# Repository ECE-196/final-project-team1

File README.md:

# Final Project

This is where you and your team will place design documents, notes, research, etc.

We want to see your individual contributions and progress over time, so make sure each of
you contribute substantially. We will look at the commit history to see your contributions.

# Submission

1. All your work!

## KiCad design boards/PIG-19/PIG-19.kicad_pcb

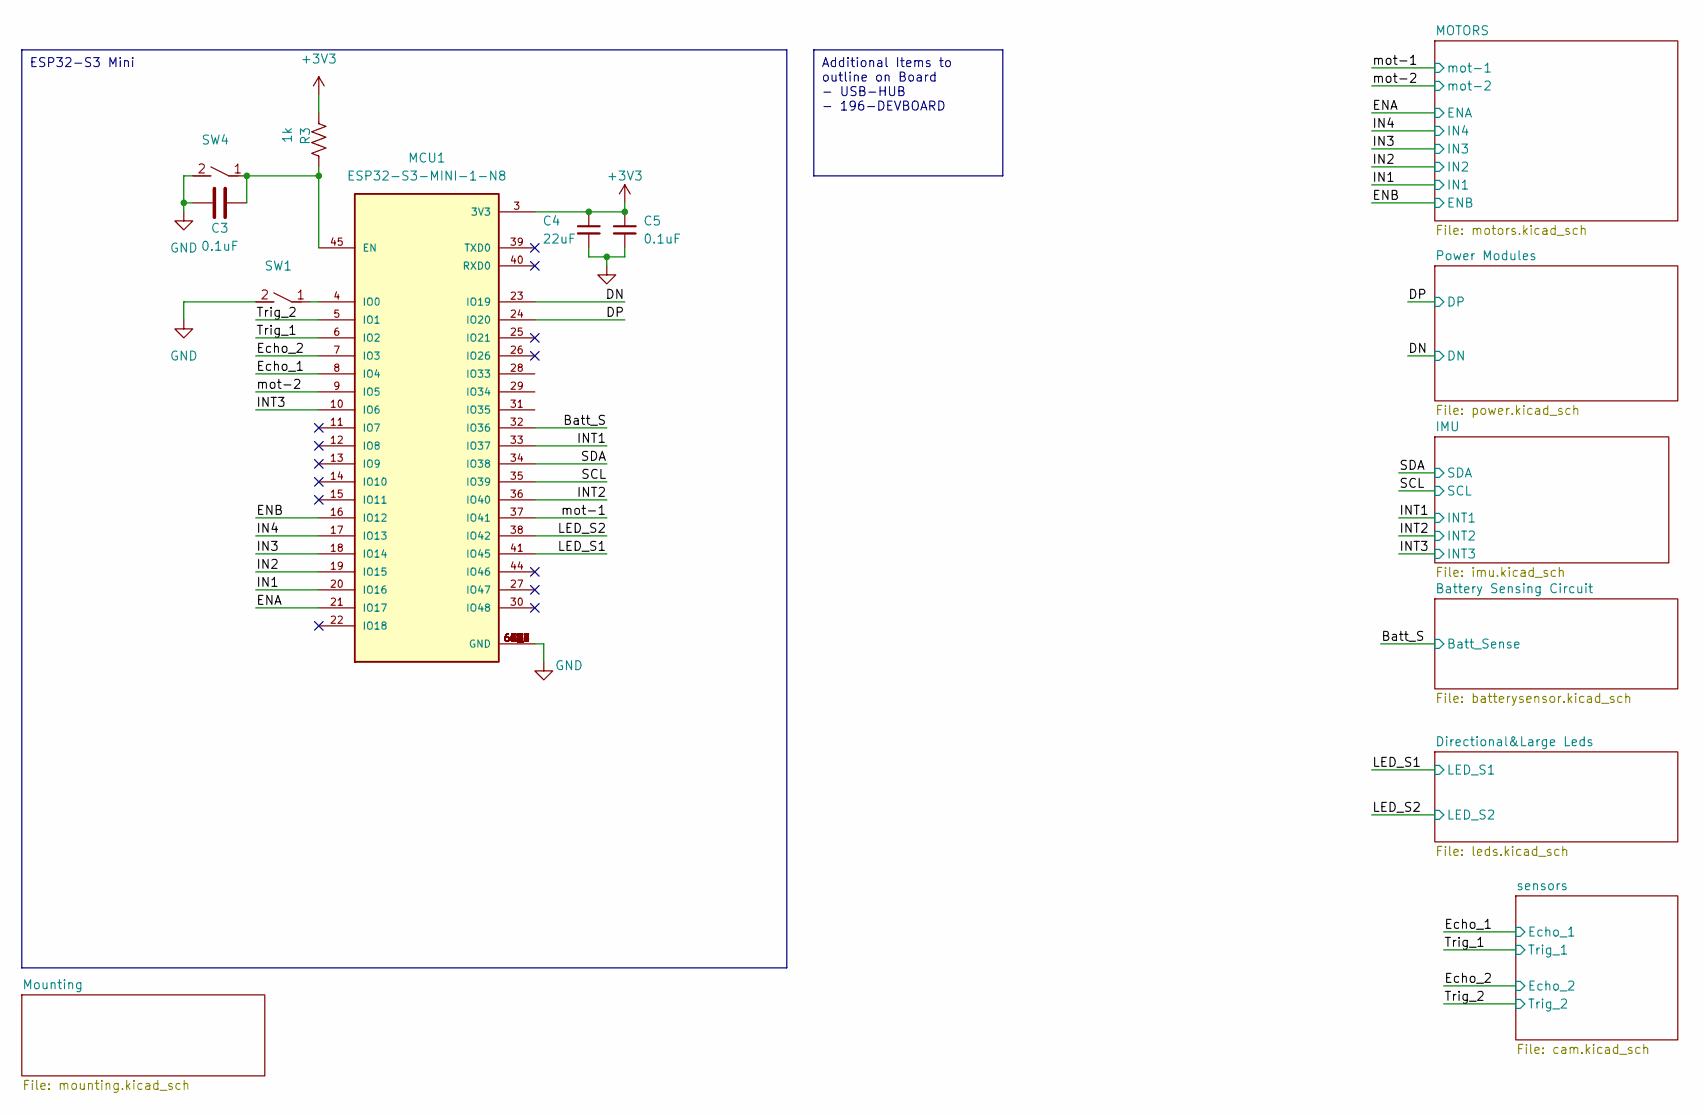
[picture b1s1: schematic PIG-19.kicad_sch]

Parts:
C3, C5: 0.1uF; C_0603_1608Metric
C4: 22uF; C_0603_1608Metric
MCU1: ESP32-S3-MINI-1-N8; XCVR_ESP32-S3-MINI-1-N8; PARTREV v0.6
R3: 1k; R_0603_1608Metric
SW1, SW4: rockerSwitch-434133025816

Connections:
+3V3: C4.1, C5.1, MCU1.3 (3V3), R3.2; also elsewhere on the board
/Batt_S: MCU1.32 (IO36); also elsewhere on the board
/DN: MCU1.23 (IO19); also elsewhere on the board
/DP: MCU1.24 (IO20); also elsewhere on the board
/ENA: MCU1.21 (IO17); also elsewhere on the board
/ENB: MCU1.16 (IO12); also elsewhere on the board
/Echo_1: MCU1.8 (IO4); also elsewhere on the board
/Echo_2: MCU1.7 (IO3); also elsewhere on the board
/IN1: MCU1.20 (IO16); also elsewhere on the board
/IN2: MCU1.19 (IO15); also elsewhere on the board
/IN3: MCU1.18 (IO14); also elsewhere on the board
/IN4: MCU1.17 (IO13); also elsewhere on the board
/INT1: MCU1.33 (IO37); also elsewhere on the board
/INT2: MCU1.36 (IO40); also elsewhere on the board
/INT3: MCU1.10 (IO6); also elsewhere on the board
/LED_S1: MCU1.41 (IO45); also elsewhere on the board
/LED_S2: MCU1.38 (IO42); also elsewhere on the board
/SCL: MCU1.35 (IO39); also elsewhere on the board
/SDA: MCU1.34 (IO38); also elsewhere on the board
/Trig_1: MCU1.6 (IO2); also elsewhere on the board
/Trig_2: MCU1.5 (IO1); also elsewhere on the board
/mot-1: MCU1.37 (IO41); also elsewhere on the board
/mot-2: MCU1.9 (IO5); also elsewhere on the board
GND: C3.1, C4.2, C5.2, MCU1.1 (GND), MCU1.2 (GND), MCU1.42 (GND), MCU1.43 (GND), MCU1.46 (GND), MCU1.47 (GND), MCU1.48 (GND), MCU1.49 (GND), MCU1.50 (GND), MCU1.51 (GND), MCU1.52 (GND), MCU1.53 (GND), MCU1.54 (GND), MCU1.55 (GND), MCU1.56 (GND), MCU1.57 (GND), MCU1.58 (GND), MCU1.59 (GND), MCU1.60 (GND), MCU1.61 (GND), MCU1.61_1 (GND), MCU1.61_2 (GND), MCU1.61_3 (GND), MCU1.61_4 (GND), MCU1.61_5 (GND), MCU1.61_6 (GND), MCU1.61_7 (GND), MCU1.61_8 (GND), MCU1.62 (GND), MCU1.63 (GND), MCU1.64 (GND), MCU1.65 (GND), SW1.2, SW4.2; also elsewhere on the board
unnamed: C3.2, MCU1.45 (EN), R3.1, SW4.1
unnamed: MCU1.4 (IO0), SW1.1

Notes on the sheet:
ESP32-S3 Mini
Additional Items to outline on Board - USB-HUB - 196-DEVBOARD

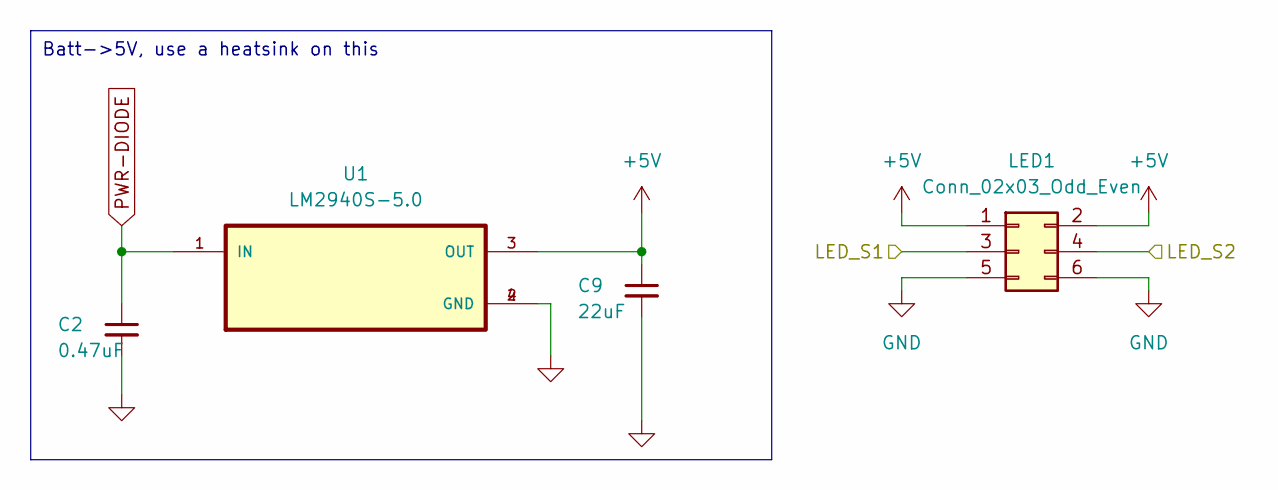
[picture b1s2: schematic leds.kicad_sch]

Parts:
C2: 0.47uF; C_0603_1608Metric
C9: 22uF; C_0603_1608Metric
LED1: Conn_02x03_Odd_Even; PinHeader_2x03_P2.54mm_Horizontal
U1: LM2940S-5.0; TO254P1524X483-4N

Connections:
+5V: C9.1, LED1.1, LED1.2, U1.3 (OUT); also elsewhere on the board
/LED_S1: LED1.3; also elsewhere on the board
/LED_S2: LED1.4; also elsewhere on the board
GND: C2.2, C9.2, LED1.5, LED1.6, U1.2 (GND), U1.4 (GND); also elsewhere on the board
PWR-DIODE: C2.1, U1.1 (IN); also elsewhere on the board

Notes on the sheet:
Batt->5V, use a heatsink on this

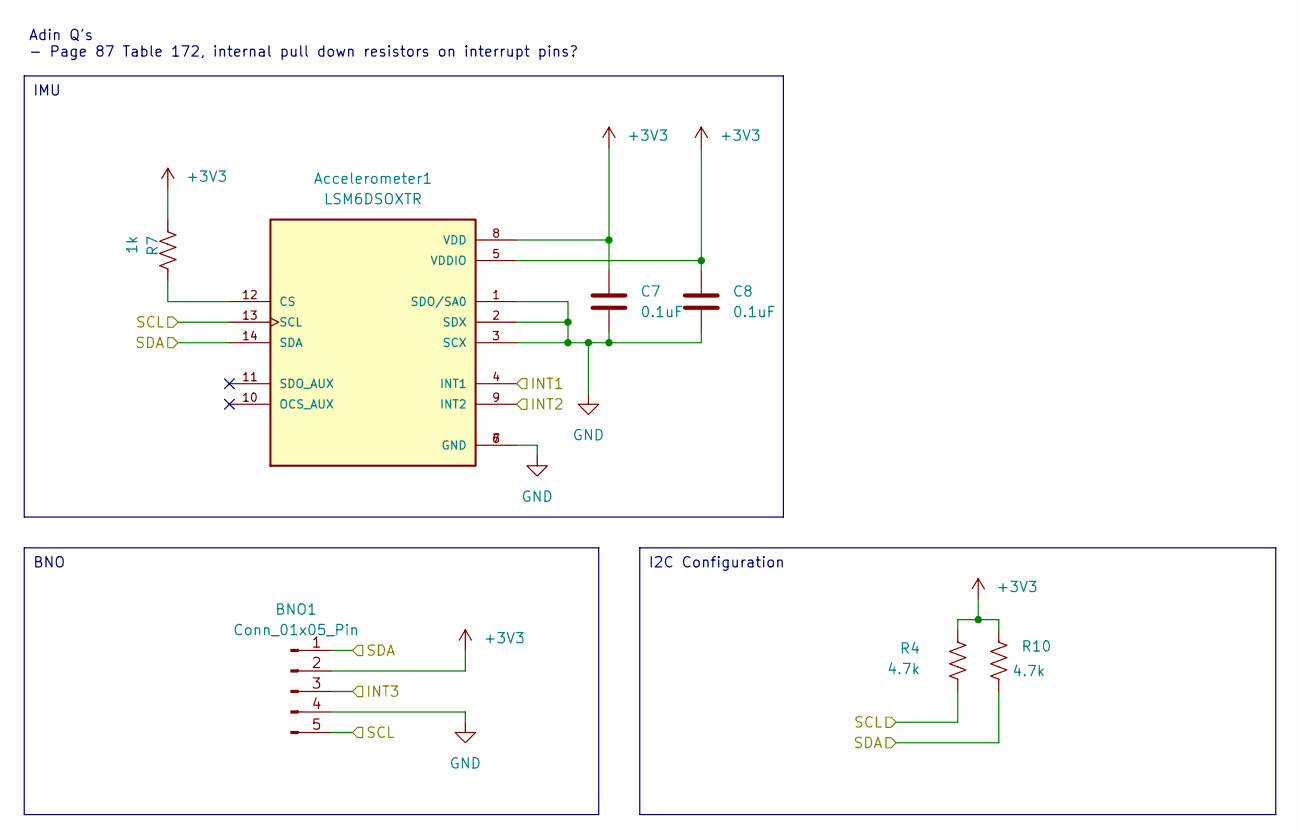
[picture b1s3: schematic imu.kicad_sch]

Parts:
Accelerometer1: LSM6DSOXTR; PQFN50P250X300X86-14N; PARTREV 3.0
BNO1: Conn_01x05_Pin; PinHeader_1x05_P2.54mm_Vertical
C7, C8: 0.1uF; C_0603_1608Metric
R4, R10: 4.7k; R_0603_1608Metric
R7: 1k; R_0603_1608Metric

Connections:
+3V3: Accelerometer1.5 (VDDIO), Accelerometer1.8 (VDD), BNO1.2, C7.1, C8.1, R4.2, R7.2, R10.2; also elsewhere on the board
/INT1: Accelerometer1.4 (INT1); also elsewhere on the board
/INT2: Accelerometer1.9 (INT2); also elsewhere on the board
/INT3: BNO1.3; also elsewhere on the board
/SCL: Accelerometer1.13 (SCL), BNO1.5, R4.1; also elsewhere on the board
/SDA: Accelerometer1.14 (SDA), BNO1.1, R10.1; also elsewhere on the board
GND: Accelerometer1.1 (SDO/SA0), Accelerometer1.2 (SDX), Accelerometer1.3 (SCX), Accelerometer1.6 (GND), Accelerometer1.7 (GND), BNO1.4, C7.2, C8.2; also elsewhere on the board
unnamed: Accelerometer1.12 (CS), R7.1

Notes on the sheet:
I2C Configuration
BNO
IMU
Adin Q's - Page 87 Table 172, internal pull down resistors on interrupt pins?

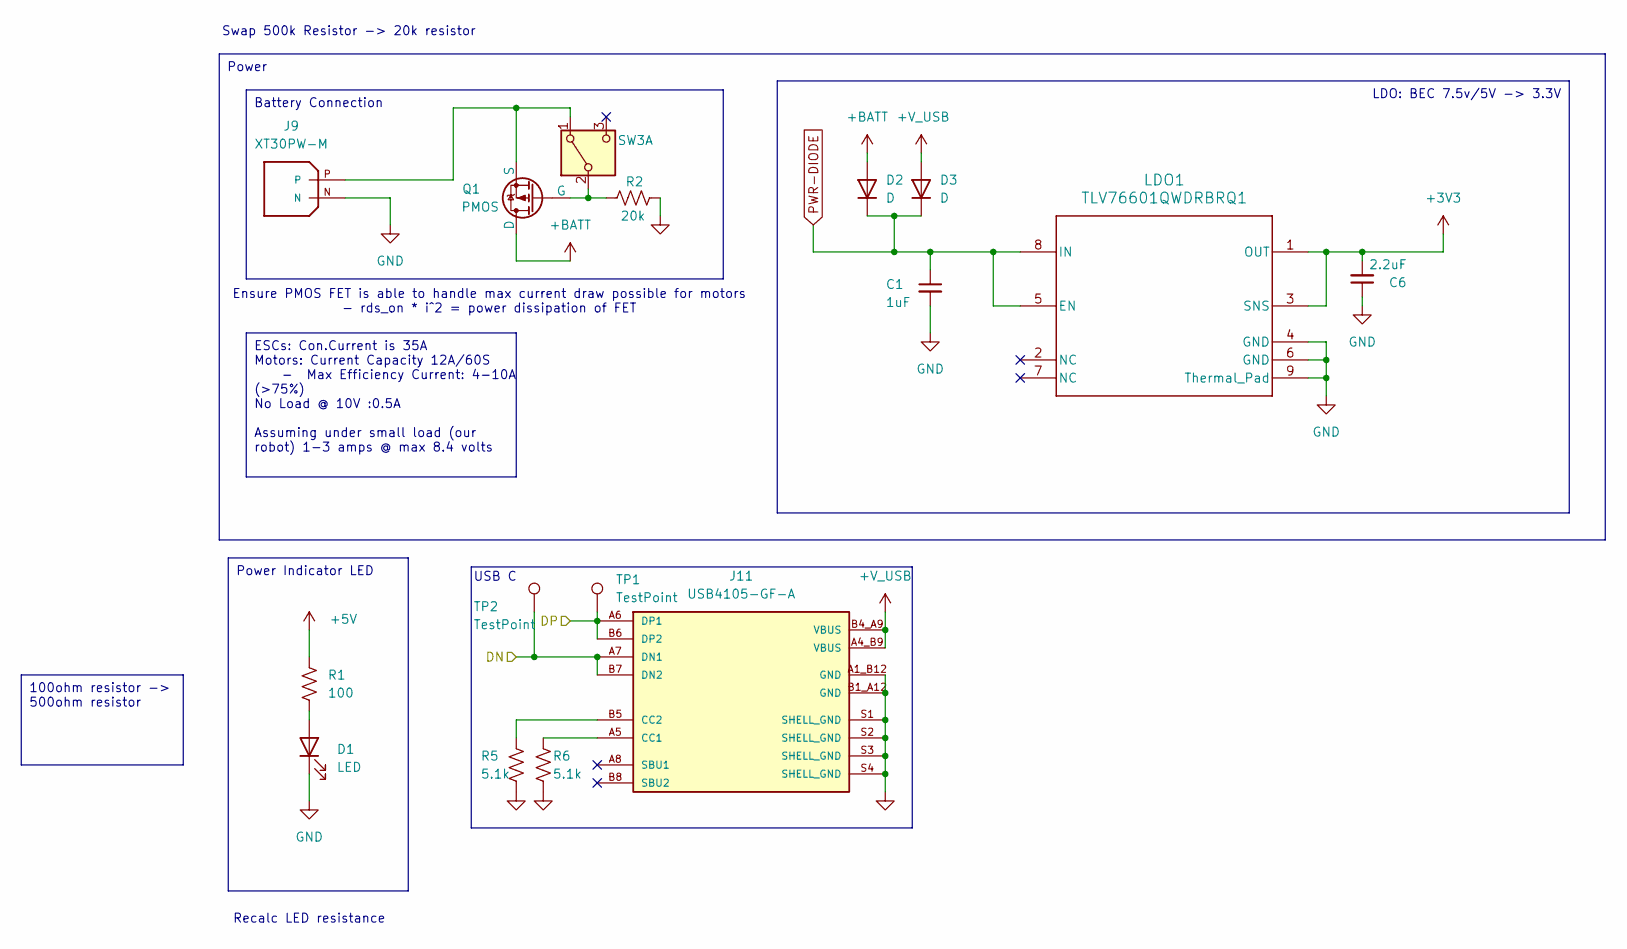
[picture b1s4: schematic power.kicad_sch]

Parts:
C1: 1uF; C_0603_1608Metric
C6: 2.2uF; C_0603_1608Metric
D1: LED; LED_0603_1608Metric
D2, D3: D; D_SOD-123F
J9: XT30PW-M; AMASS_XT30PW-M; PARTREV 1.2
J11: USB4105-GF-A; GCT_USB4105-GF-A; PARTREV A3
LDO1: TLV76601QWDRBRQ1; DRB0008J-IPC_A
Q1: PMOS; PowerPAK_SO-8_Single
R1: 100; R_0603_1608Metric
R2: 20k; R_0603_1608Metric
R5, R6: 5.1k; R_0603_1608Metric
SW3: SW_Nidec_CAS-120A1; SW_JS102011JAQN
TP1, TP2: TestPoint; TestPoint_Pad_D2.0mm

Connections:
+3V3: C6.2, LDO1.1 (OUT), LDO1.3 (SNS); also elsewhere on the board
+5V: R1.1; also elsewhere on the board
+BATT: D2.2 (A), Q1.5 (D); also elsewhere on the board
+V_USB: D3.2 (A), J11.A4_B9 (VBUS), J11.B4_A9 (VBUS)
/DN: J11.A7 (DN1), J11.B7 (DN2), TP2.1; also elsewhere on the board
/DP: J11.A6 (DP1), J11.B6 (DP2), TP1.1; also elsewhere on the board
GND: C1.2, C6.1, D1.1 (K), J9.N, J11.A1_B12 (GND), J11.B1_A12 (GND), J11.S1 (SHELL_GND), J11.S2 (SHELL_GND), J11.S3 (SHELL_GND), J11.S4 (SHELL_GND), LDO1.4 (GND), LDO1.6 (GND), LDO1.9 (Thermal_Pad), R2.2, R5.2, R6.2; also elsewhere on the board
unnamed: D1.2 (A), R1.2
unnamed: J11.A5 (CC1), R6.1
unnamed: J11.B5 (CC2), R5.1
unnamed: Q1.4 (G), R2.1, SW3.2 (B)
unnamed: J9.P, Q1.1 (S), Q1.2 (S), Q1.3 (S), SW3.1 (A)
PWR-DIODE: C1.1, D2.1 (K), D3.1 (K), LDO1.5 (EN), LDO1.8 (IN); also elsewhere on the board

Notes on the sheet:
LDO: BEC 7.5v/5V -> 3.3V
Battery Connection
100ohm resistor -> 500ohm resistor
ESCs: Con.Current is 35A Motors: Current Capacity 12A/60S - Max Efficiency Current: 4-10A (>75%) No Load @ 10V :0.5A Assuming under small load (our robot) 1-3 amps @ max 8.4 volts
Power Indicator LED
Power
Swap 500k Resistor -> 20k resistor
Recalc LED resistance
Ensure PMOS FET is able to handle max current draw possible for motors - rds_on * i^2 = power dissipation of FET
USB C

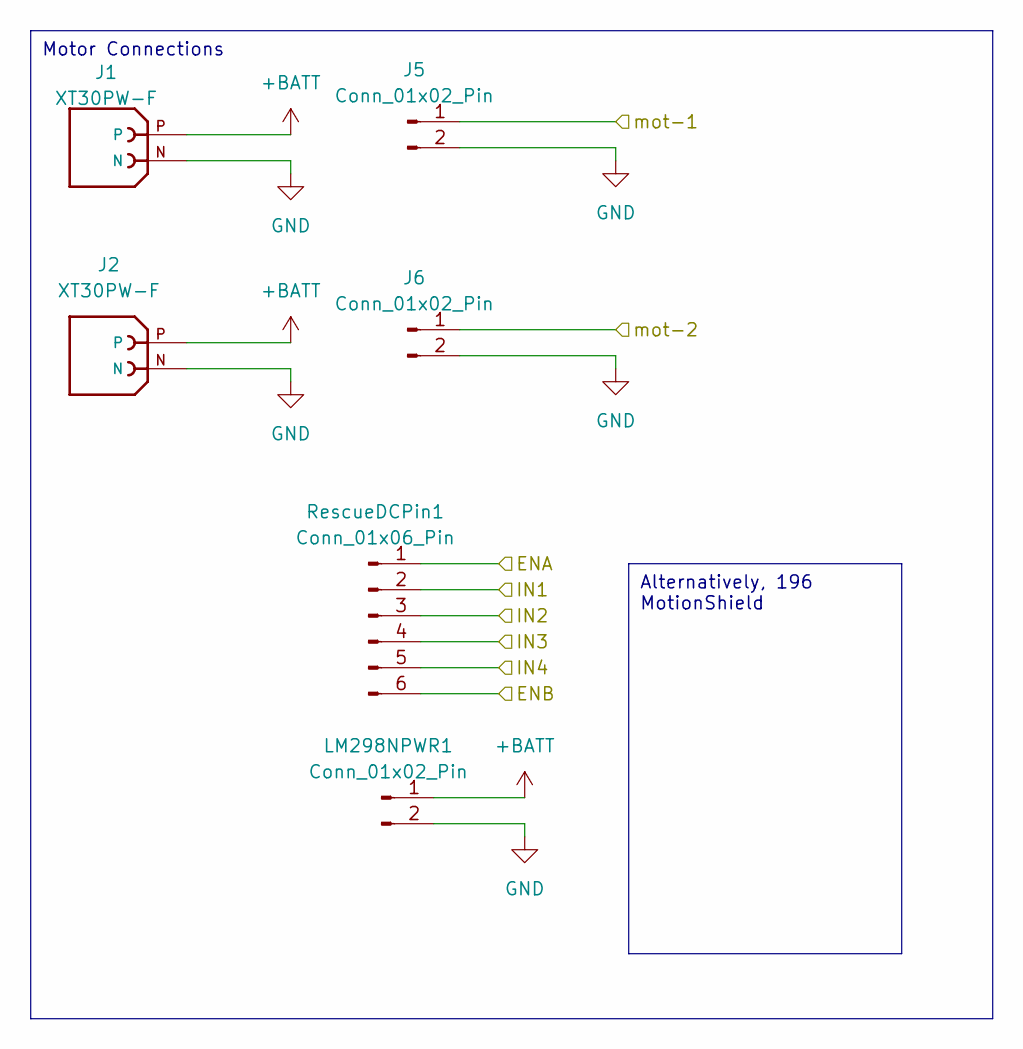
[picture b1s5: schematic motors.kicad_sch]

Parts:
J1, J2: XT30PW-F; AMASS_XT30PW-F; PARTREV 1.2
J5, J6: Conn_01x02_Pin; PinHeader_1x02_P2.54mm_Horizontal
LM298NPWR1: Conn_01x02_Pin; PinHeader_1x02_P2.54mm_Vertical
RescueDCPin1: Conn_01x06_Pin; PinHeader_1x06_P2.54mm_Vertical

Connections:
+BATT: J1.P, J2.P, LM298NPWR1.1; also elsewhere on the board
/ENA: RescueDCPin1.1; also elsewhere on the board
/ENB: RescueDCPin1.6; also elsewhere on the board
/IN1: RescueDCPin1.2; also elsewhere on the board
/IN2: RescueDCPin1.3; also elsewhere on the board
/IN3: RescueDCPin1.4; also elsewhere on the board
/IN4: RescueDCPin1.5; also elsewhere on the board
/mot-1: J5.1; also elsewhere on the board
/mot-2: J6.1; also elsewhere on the board
GND: J1.N, J2.N, J5.2, J6.2, LM298NPWR1.2; also elsewhere on the board

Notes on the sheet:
Motor Connections
Alternatively, 196 MotionShield

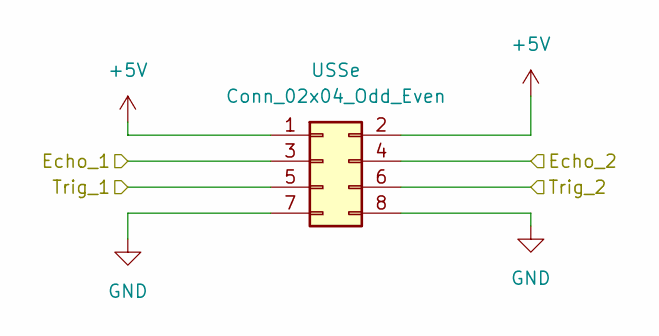
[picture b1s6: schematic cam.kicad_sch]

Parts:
USSe: Conn_02x04_Odd_Even; PinHeader_2x04_P2.54mm_Horizontal

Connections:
unnamed: USSe.1, USSe.2
unnamed: USSe.7, USSe.8

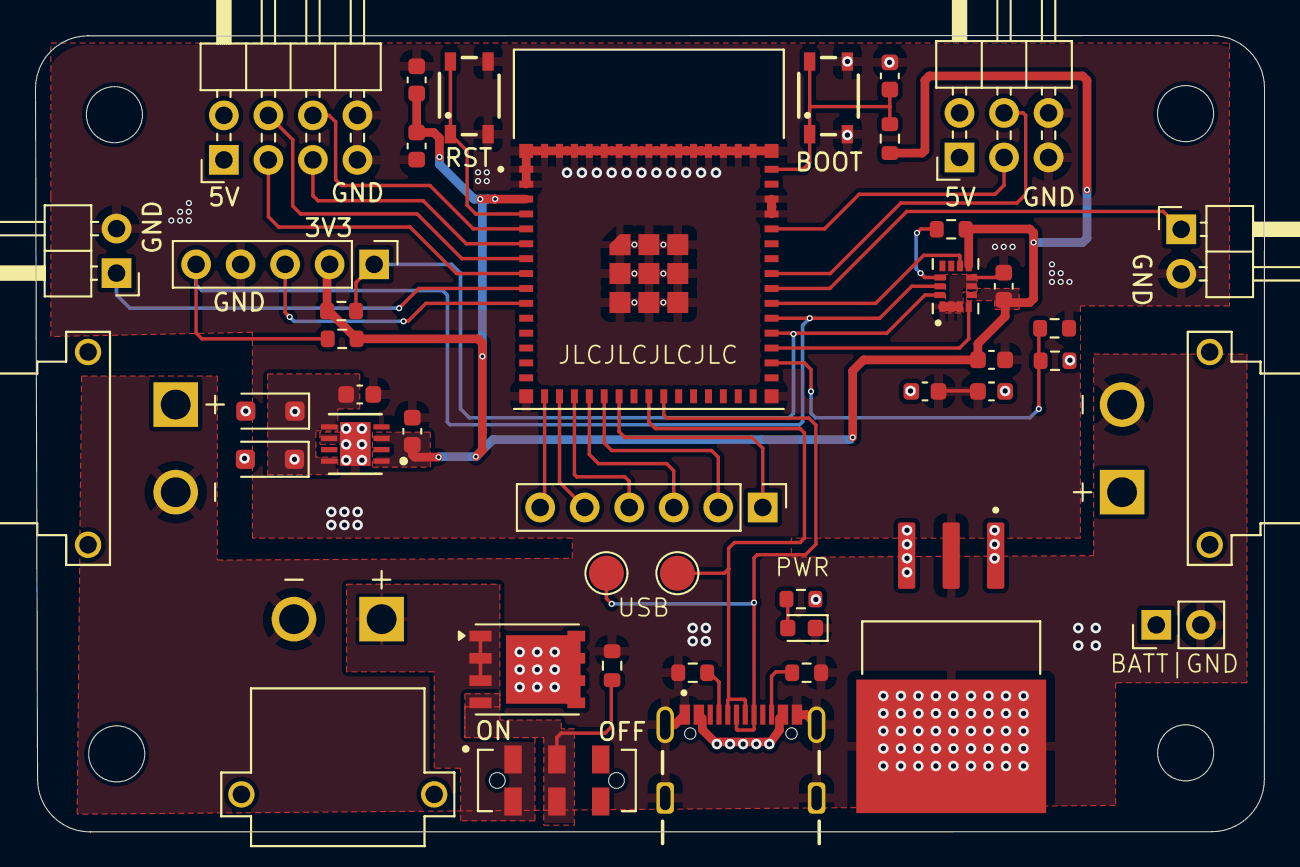
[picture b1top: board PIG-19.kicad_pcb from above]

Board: 4 copper layers, 70.1 x 45.4 mm, 47 parts (0 on the bottom side), 36 nets.

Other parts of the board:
H1, H2, H3, H4: MountingHole; MountingHole_3.2mm_M3_DIN965
R8: 1M; R_0603_1608Metric
R9: 500k; R_0603_1608Metric
USS1: Conn_02x04_Odd_Even; PinHeader_2x04_P2.54mm_Horizontal

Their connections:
+5V: USS1.1, USS1.2; also elsewhere on the board
+BATT: R8.1; also elsewhere on the board
/Batt_S: R8.2, R9.1; also elsewhere on the board
/Echo_1: USS1.3; also elsewhere on the board
/Echo_2: USS1.4; also elsewhere on the board
/Trig_1: USS1.5; also elsewhere on the board
/Trig_2: USS1.6; also elsewhere on the board
GND: R9.2, USS1.7, USS1.8; also elsewhere on the board

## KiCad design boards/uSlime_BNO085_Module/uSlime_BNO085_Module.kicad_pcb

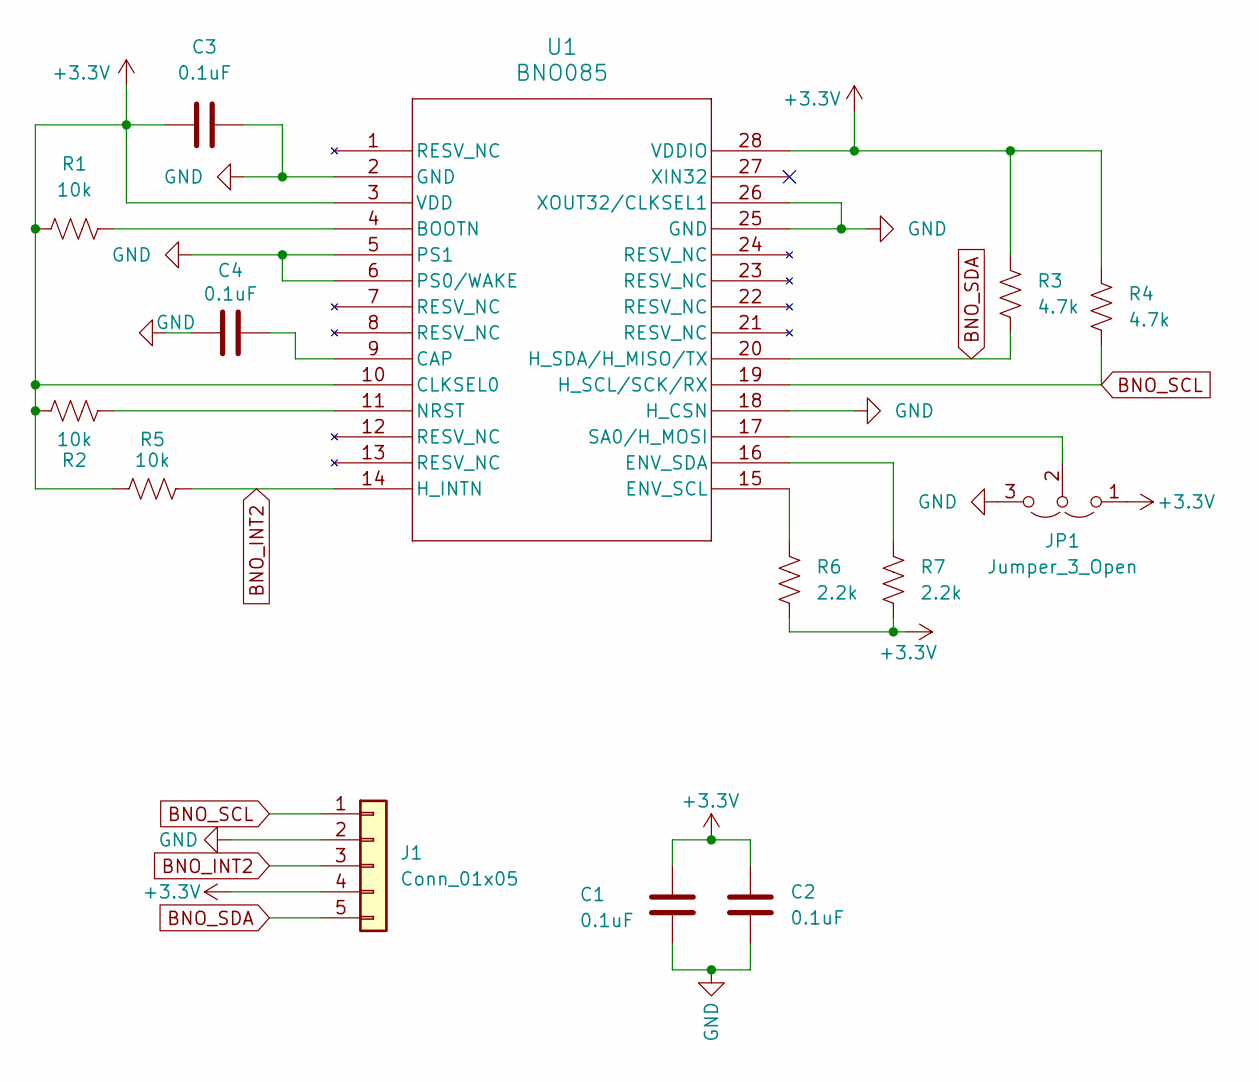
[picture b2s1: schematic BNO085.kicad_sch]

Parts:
C1, C2, C3, C4: 0.1uF; C_0603_1608Metric
J1: Conn_01x05; PinHeader_1x05_P2.54mm_Vertical
JP1: Jumper_3_Open; SolderJumper-3_P1.3mm_Open_RoundedPad1.0x1.5mm
R1, R2, R5: 10k; R_0603_1608Metric
R3, R4: 4.7k; R_0603_1608Metric
R6, R7: 2.2k; R_0603_1608Metric
U1: BNO085; updatedBNO

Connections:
+3.3V: C1.2, C2.2, C3.1, J1.4, JP1.1 (A), R1.1, R2.2, R3.1, R4.1, R5.1, R6.2, R7.2, U1.3 (VDD), U1.10 (CLKSEL0), U1.28 (VDDIO)
BNO_INT2: J1.3, R5.2, U1.14 (H_INTN)
BNO_SCL: J1.1, R4.2, U1.19 (H_SCL/SCK/RX)
BNO_SDA: J1.5, R3.2, U1.20 (H_SDA/H_MISO/TX)
GND: C1.1, C2.1, C3.2, C4.1, J1.2, JP1.3 (B), U1.2 (GND), U1.5 (PS1), U1.6 (PS0/WAKE), U1.18 (H_CSN), U1.25 (GND), U1.26 (XOUT32/CLKSEL1)
unnamed: JP1.2 (C), U1.17 (SA0/H_MOSI)
unnamed: R1.2, U1.4 (BOOTN)
unnamed: C4.2, U1.9 (CAP)
unnamed: R6.1, U1.15 (ENV_SCL)
unnamed: R7.1, U1.16 (ENV_SDA)
unnamed: R2.1, U1.11 (NRST)

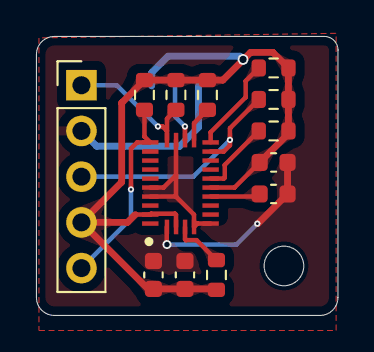
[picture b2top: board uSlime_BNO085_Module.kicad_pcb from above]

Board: 2 copper layers, 16.8 x 15.5 mm, 14 parts (1 on the bottom side), 11 nets.

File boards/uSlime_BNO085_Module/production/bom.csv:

Designator,Footprint,Quantity,Value,LCSC Part #
"C1, C2, C3, C4",0603,4,0.1uF,
J1,PinHeader_1x05_P2.54mm_Vertical,1,Conn_01x05,
"R1, R2, R5",0603,3,10k,
"R3, R4, R6, R7",0603,4,2.2k,
U1,updatedBNO,1,BNO085,

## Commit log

2024-10-24 init commit
2024-10-24 another seutp
2024-10-27 V1 of PCB
2024-10-28 board to be reviewed
2024-10-28 I2C pull up resistors
2024-10-28 commit for adin to review
2024-10-28 add break out board schemetic
2024-10-29 board updates
2024-10-29 update pcb design
2024-10-31 update datasheets
2024-10-31 Final Board Revision - pls order this one TAs
2024-10-31 Order & Check TAs pls ty ty
2024-10-31 organize file
2024-10-31 other PIG-19 & BNO Board pls, ty
2024-10-31 PIG-19 & BNO085 boards pls order both ty ty
2024-10-31 order pig19 and bno boards pls
2024-11-01 order this one
2024-11-01 Update uSlime_BNO085_Module.kicad_pcb
    use 15 mil power line
2024-11-01 gerber update
2024-11-01 update Mian gerber
2024-11-01 update schmetic
2024-11-01 do not ignore bom
2024-11-01 Added BOM for main board
2024-11-01 this bom file to order pls
2024-11-01 update bno BOM
2024-11-06 add pcb measurement
2024-11-19 update software
2024-11-22 update config
2024-11-23 The finally working version of reading raw data in main.cpp
2024-11-23 create the working folder for the breakout board, currently just a copy of the main board
2024-11-25 updatemain
2024-11-25 update calibration
2024-11-25 Updated Audio Playing functionality, tested working in main.cpp
2024-11-25 Update configuration for the breakout board
2024-11-25 a clean generic version for reading raw BNO and intergrate audio play
2024-11-25 bug fixed
2024-11-25 update ignore
2024-11-25 updategitignore
2024-11-25 Update successfully reading and printing BNO data from breakout board
2024-11-25 update a bunch of testing lib and dependencies, trying to solve BLE on espc6
2024-11-26 update version
2024-11-26 Push BLE HelloWorld basic function working code
2024-12-01 calibration UPDate
2024-12-02 update location detection, and audio pin
2024-12-03 update main so there is not bluetooth realated parts in it
2024-12-03 Incorporate BLE feature into current data-parsed version code
2024-12-04 update main.cpp of mainboard
2024-12-19 update main function
